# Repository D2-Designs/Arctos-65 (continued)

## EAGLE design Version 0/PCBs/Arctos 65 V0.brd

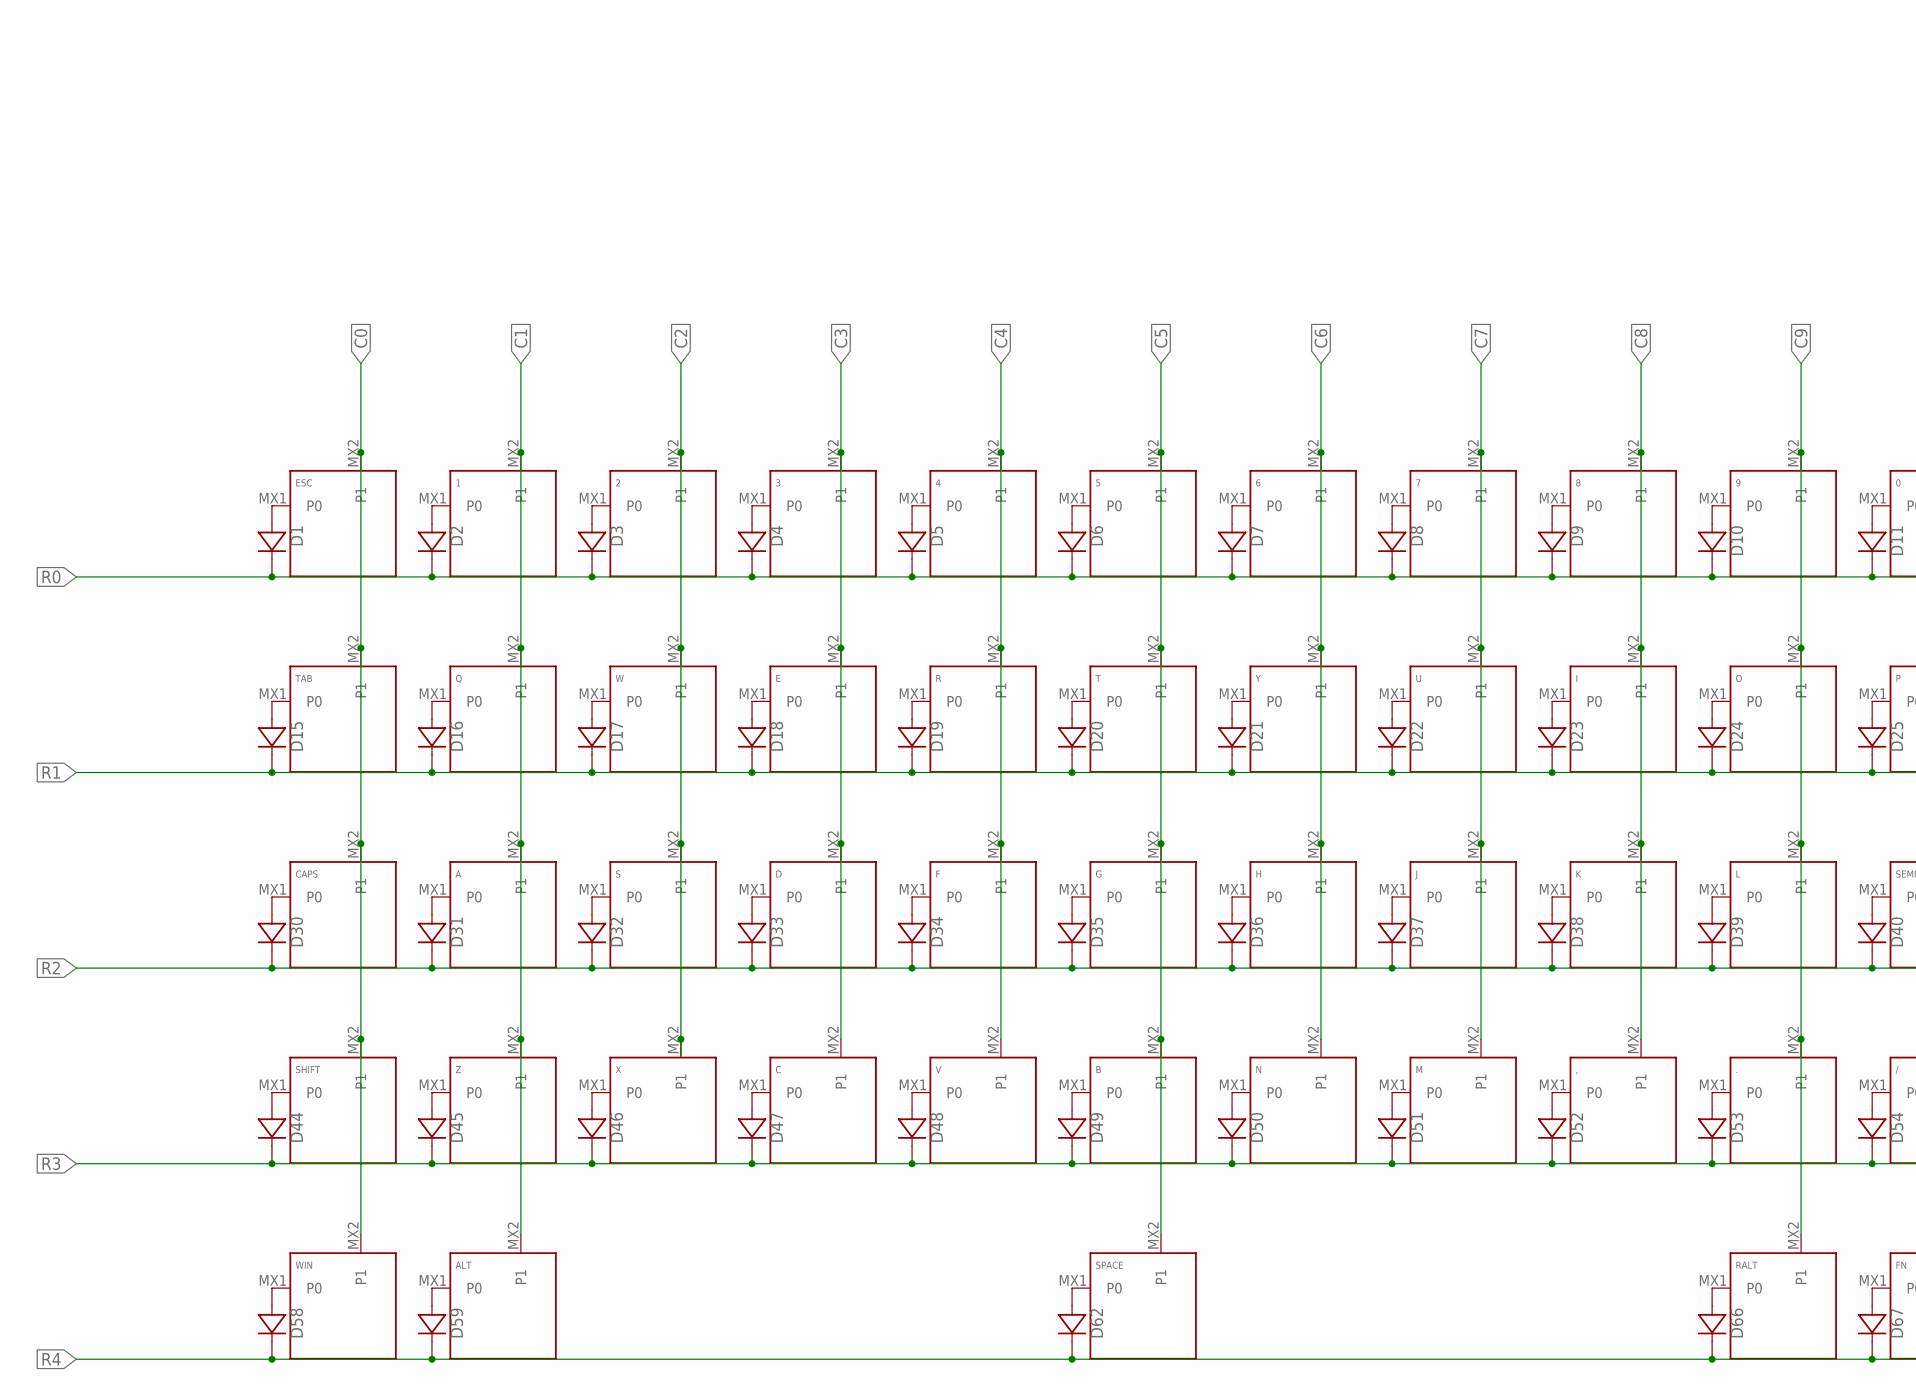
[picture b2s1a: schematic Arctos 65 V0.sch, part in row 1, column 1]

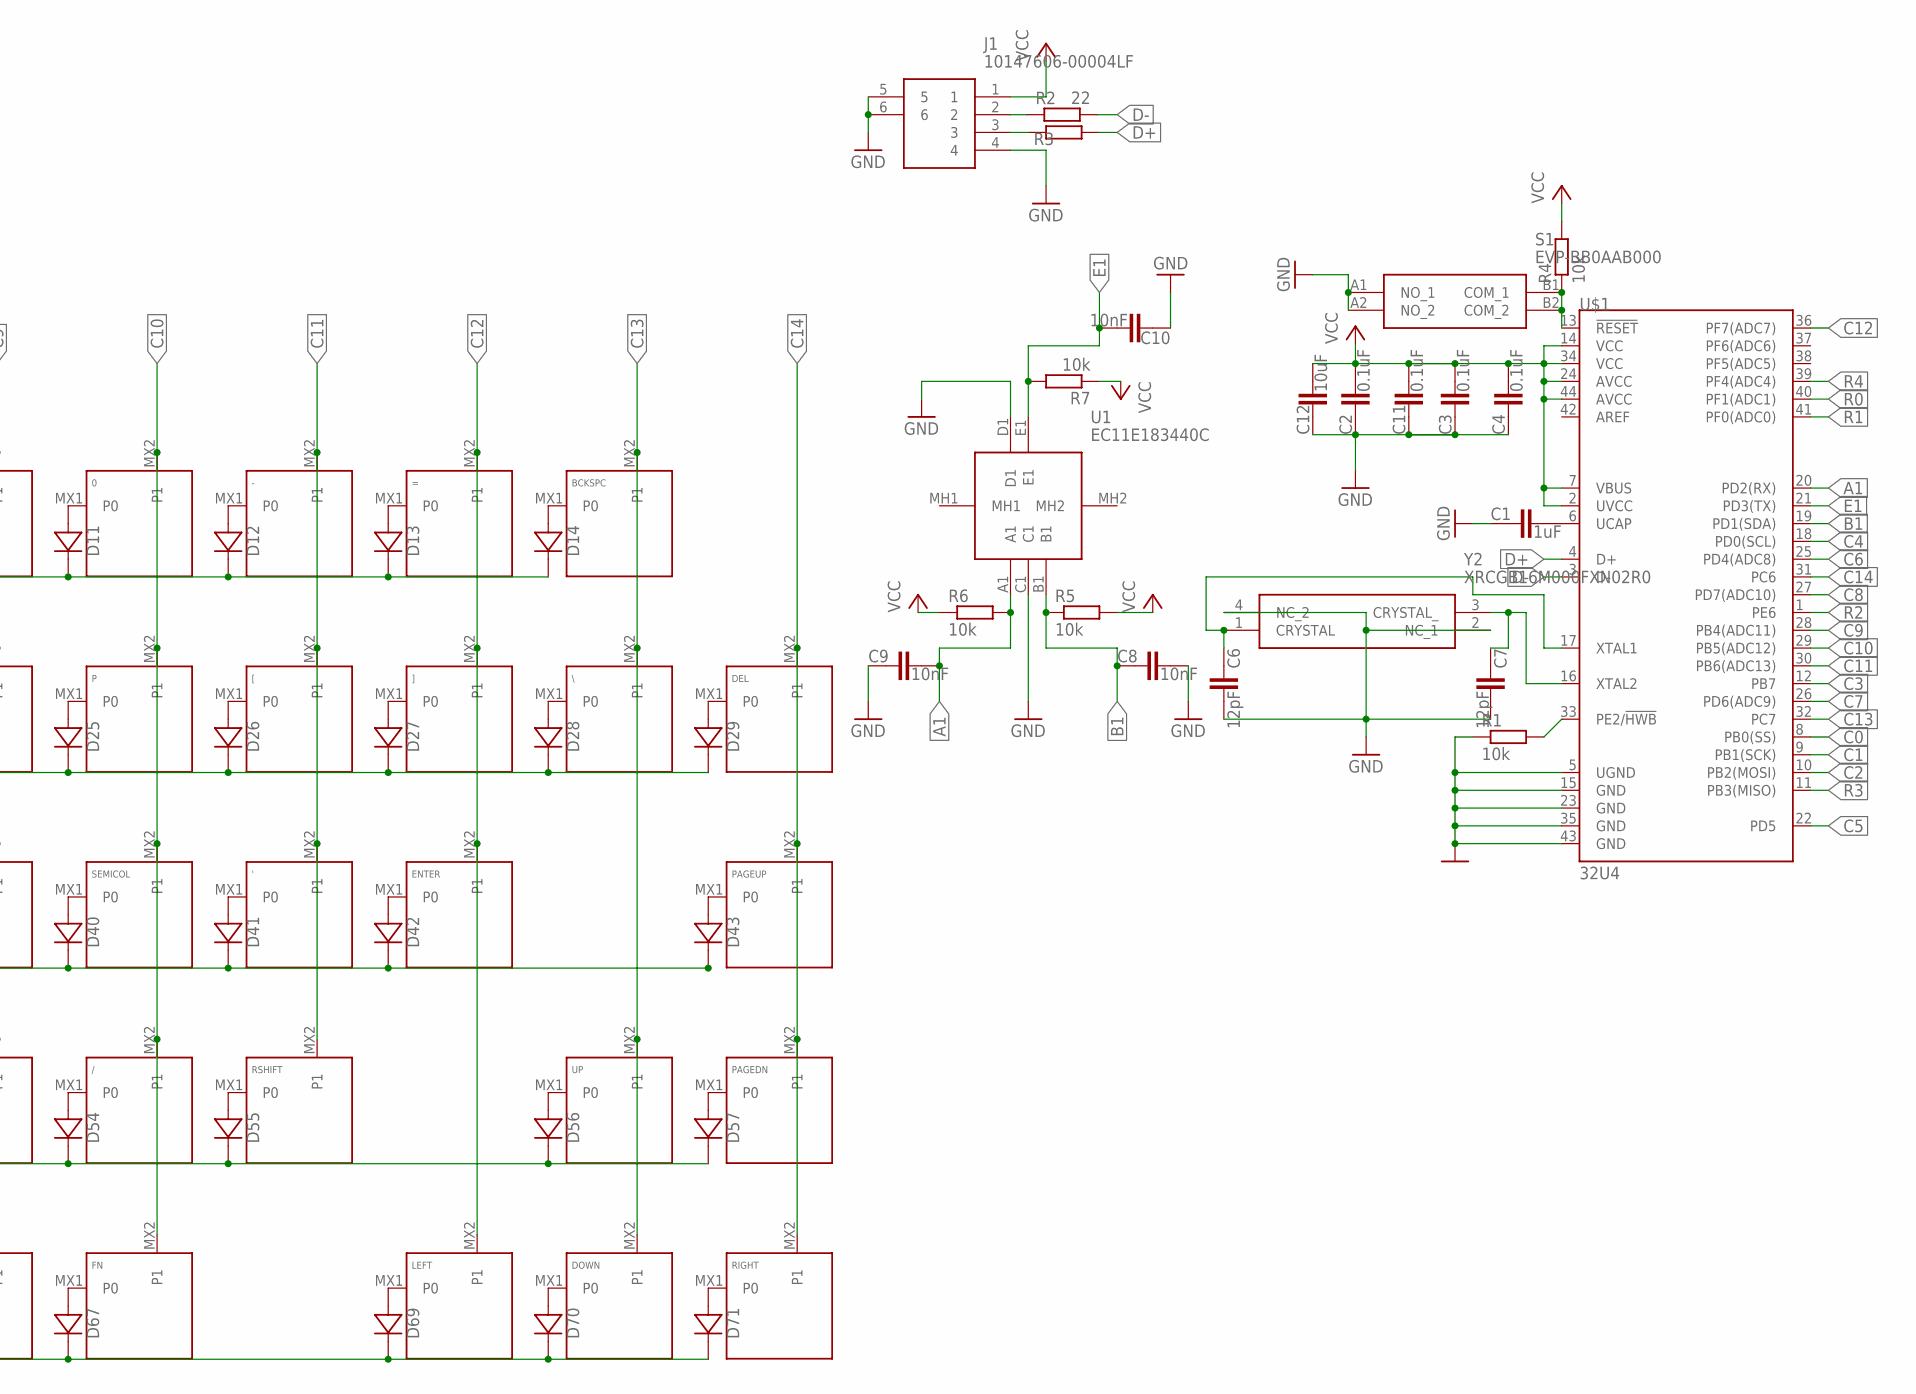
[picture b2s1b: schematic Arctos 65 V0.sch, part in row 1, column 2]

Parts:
0, 1, 2, 3, 4, 5, 6, 7, 8, 9, .: KEYSWITCH-PLAIN-MXHSPCB-1U; MXHSPCB-1U
': KEYSWITCH-PLAIN-MXHSPCB-1U; MXHSPCB-1U
,: KEYSWITCH-PLAIN-MXHSPCB-1U; MXHSPCB-1U
-: KEYSWITCH-PLAIN-MXHSPCB-1U; MXHSPCB-1U
/: KEYSWITCH-PLAIN-MXHSPCB-1U; MXHSPCB-1U
=: KEYSWITCH-PLAIN-MXHSPCB-1U; MXHSPCB-1U
A: KEYSWITCH-PLAIN-MXHSPCB-1U; MXHSPCB-1U
ALT: KEYSWITCH-PLAIN-MXHSPCB-1U; MXHSPCB-1U
B: KEYSWITCH-PLAIN-MXHSPCB-1U; MXHSPCB-1U
BCKSPC: KEYSWITCH-PLAIN-MXHSPCB-2U; MXHSPCB-2U
C: KEYSWITCH-PLAIN-MXHSPCB-1U; MXHSPCB-1U
C1: 1uF; C0603
C2, C3, C4, C11: 0.1uF; C0603
C6, C7: 12pF; C0603
C8, C9, C10: 10nF; C0603
C12: 10uF; C0603
CAPS: KEYSWITCH-PLAIN-MXHSPCB-1U; MXHSPCB-1U
D: KEYSWITCH-PLAIN-MXHSPCB-1U; MXHSPCB-1U
D1, D2, D3, D4, D5, D6, D7, D8, D9, D10, D11, D12, D13, D14, D15, D16, D17, D18, D19, D20, D21, D22, D23, D24, D25, D26, D27, D28, D29, D30, D31, D32, D33, D34, D35, D36, D37, D38, D39, D40, D41, D42, D43, D44, D45, D46, D47, D48, D49, D50, D51, D52, D53, D54, D55, D56, D57, D58, D59, D62, D66, D67, D69, D70, D71: DIODE-SOD-123; SOD-123
DEL: KEYSWITCH-PLAIN-MXHSPCB-1U; MXHSPCB-1U
DOWN: KEYSWITCH-PLAIN-MXHSPCB-1U; MXHSPCB-1U
E: KEYSWITCH-PLAIN-MXHSPCB-1U; MXHSPCB-1U
ENTER: KEYSWITCH-PLAIN-MXHSPCB-2U; MXHSPCB-2U
ESC: KEYSWITCH-PLAIN-MXHSPCB-1U; MXHSPCB-1U
F: KEYSWITCH-PLAIN-MXHSPCB-1U; MXHSPCB-1U
FN: KEYSWITCH-PLAIN-MXHSPCB-1U; MXHSPCB-1U
G: KEYSWITCH-PLAIN-MXHSPCB-1U; MXHSPCB-1U
H: KEYSWITCH-PLAIN-MXHSPCB-1U; MXHSPCB-1U
I: KEYSWITCH-PLAIN-MXHSPCB-1U; MXHSPCB-1U
J: KEYSWITCH-PLAIN-MXHSPCB-1U; MXHSPCB-1U
J1: 10147606-00004LF; 1014760600004LF
K: KEYSWITCH-PLAIN-MXHSPCB-1U; MXHSPCB-1U
L: KEYSWITCH-PLAIN-MXHSPCB-1U; MXHSPCB-1U
LEFT: KEYSWITCH-PLAIN-MXHSPCB-1U; MXHSPCB-1U
M: KEYSWITCH-PLAIN-MXHSPCB-1U; MXHSPCB-1U
N: KEYSWITCH-PLAIN-MXHSPCB-1U; MXHSPCB-1U
O: KEYSWITCH-PLAIN-MXHSPCB-1U; MXHSPCB-1U
P: KEYSWITCH-PLAIN-MXHSPCB-1U; MXHSPCB-1U
PAGEDN: KEYSWITCH-PLAIN-MXHSPCB-1U; MXHSPCB-1U
PAGEUP: KEYSWITCH-PLAIN-MXHSPCB-1U; MXHSPCB-1U
Q: KEYSWITCH-PLAIN-MXHSPCB-1U; MXHSPCB-1U
R: KEYSWITCH-PLAIN-MXHSPCB-1U; MXHSPCB-1U
R1, R4, R5, R6, R7: 10k; R0603
R2, R3: 22; R0603
RALT: KEYSWITCH-PLAIN-MXHSPCB-1U; MXHSPCB-1U
RIGHT: KEYSWITCH-PLAIN-MXHSPCB-1U; MXHSPCB-1U
RSHIFT: KEYSWITCH-PLAIN-MXHSPCB-1U; MXHSPCB-1U
S: KEYSWITCH-PLAIN-MXHSPCB-1U; MXHSPCB-1U
S1: EVP-BB0AAB000; EVPBB0AAB000
SEMICOL: KEYSWITCH-PLAIN-MXHSPCB-1U; MXHSPCB-1U
SHIFT: KEYSWITCH-PLAIN-MXHSPCB-2U; MXHSPCB-2U
SPACE: KEYSWITCH-PLAIN-MXHSPCB-7U-FLIPPED; MXHSPCB-7U-FLIPPED
T: KEYSWITCH-PLAIN-MXHSPCB-1U; MXHSPCB-1U
TAB: KEYSWITCH-PLAIN-MXHSPCB-1U; MXHSPCB-1U
U: KEYSWITCH-PLAIN-MXHSPCB-1U; MXHSPCB-1U
U1: EC11E183440C
U$1: 32U4; TQFP44
UP: KEYSWITCH-PLAIN-MXHSPCB-1U; MXHSPCB-1U
V: KEYSWITCH-PLAIN-MXHSPCB-1U; MXHSPCB-1U
W: KEYSWITCH-PLAIN-MXHSPCB-1U; MXHSPCB-1U
WIN: KEYSWITCH-PLAIN-MXHSPCB-1U; MXHSPCB-1U
X: KEYSWITCH-PLAIN-MXHSPCB-1U; MXHSPCB-1U
Y: KEYSWITCH-PLAIN-MXHSPCB-1U; MXHSPCB-1U
Y2: XRCGB16M000FXN02R0
Z: KEYSWITCH-PLAIN-MXHSPCB-1U; MXHSPCB-1U
[: KEYSWITCH-PLAIN-MXHSPCB-1U; MXHSPCB-1U
\: KEYSWITCH-PLAIN-MXHSPCB-1U; MXHSPCB-1U
]: KEYSWITCH-PLAIN-MXHSPCB-1U; MXHSPCB-1U

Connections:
A1: C9.2, R6.2, U1.A1, U$1.20 (PD2(RX))
B1: C8.1, R5.1, U1.B1, U$1.19 (PD1(SDA))
C0: CAPS.MX2 (P1), ESC.MX2 (P1), SHIFT.MX2 (P1), TAB.MX2 (P1), U$1.8 (PB0(SS)), WIN.MX2 (P1)
C1: 1.MX2 (P1), A.MX2 (P1), ALT.MX2 (P1), Q.MX2 (P1), U$1.9 (PB1(SCK)), Z.MX2 (P1)
C2: 2.MX2 (P1), S.MX2 (P1), U$1.10 (PB2(MOSI)), W.MX2 (P1), X.MX2 (P1)
C3: 3.MX2 (P1), C.MX2 (P1), D.MX2 (P1), E.MX2 (P1), U$1.12 (PB7)
C4: 4.MX2 (P1), F.MX2 (P1), R.MX2 (P1), U$1.18 (PD0(SCL)), V.MX2 (P1)
C5: 5.MX2 (P1), B.MX2 (P1), G.MX2 (P1), SPACE.MX2 (P1), T.MX2 (P1), U$1.22 (PD5)
C6: 6.MX2 (P1), H.MX2 (P1), N.MX2 (P1), U$1.25 (PD4(ADC8)), Y.MX2 (P1)
C7: 7.MX2 (P1), J.MX2 (P1), M.MX2 (P1), U.MX2 (P1), U$1.26 (PD6(ADC9))
C8: 8.MX2 (P1), ,.MX2 (P1), I.MX2 (P1), K.MX2 (P1), U$1.27 (PD7(ADC10))
C9: 9.MX2 (P1), ..MX2 (P1), L.MX2 (P1), O.MX2 (P1), RALT.MX2 (P1), U$1.28 (PB4(ADC11))
C10: 0.MX2 (P1), /.MX2 (P1), FN.MX2 (P1), P.MX2 (P1), SEMICOL.MX2 (P1), U$1.29 (PB5(ADC12))
C11: '.MX2 (P1), -.MX2 (P1), RSHIFT.MX2 (P1), U$1.30 (PB6(ADC13)), [.MX2 (P1)
C12: =.MX2 (P1), ENTER.MX2 (P1), LEFT.MX2 (P1), U$1.36 (PF7(ADC7)), ].MX2 (P1)
C13: BCKSPC.MX2 (P1), DOWN.MX2 (P1), U$1.32 (PC7), UP.MX2 (P1), \.MX2 (P1)
C14: DEL.MX2 (P1), PAGEDN.MX2 (P1), PAGEUP.MX2 (P1), RIGHT.MX2 (P1), U$1.31 (PC6)
D+: R3.2, U$1.4 (D+)
D-: R2.2, U$1.3 (D-)
E1: C10.2, R7.2, U1.E1, U$1.21 (PD3(TX))
GND: C1.1, C2.1, C3.1, C4.1, C6.2, C7.2, C8.2, C9.1, C10.1, C11.1, C12.1, J1.4, J1.5, J1.6, R1.1, S1.A1 (NO_1), S1.A2 (NO_2), U1.C1, U1.D1, U$1.5 (UGND), U$1.15 (GND), U$1.23 (GND), U$1.35 (GND), U$1.43 (GND), Y2.2 (NC_1), Y2.4 (NC_2)
unnamed: 4.MX1 (P0), D5.A
unnamed: 5.MX1 (P0), D6.A
unnamed: 6.MX1 (P0), D7.A
unnamed: 7.MX1 (P0), D8.A
unnamed: 8.MX1 (P0), D9.A
unnamed: 9.MX1 (P0), D10.A
unnamed: 0.MX1 (P0), D11.A
unnamed: -.MX1 (P0), D12.A
unnamed: =.MX1 (P0), D13.A
unnamed: BCKSPC.MX1 (P0), D14.A
unnamed: D15.A, TAB.MX1 (P0)
unnamed: D16.A, Q.MX1 (P0)
unnamed: D17.A, W.MX1 (P0)
unnamed: D18.A, E.MX1 (P0)
unnamed: D19.A, R.MX1 (P0)
unnamed: D20.A, T.MX1 (P0)
unnamed: D21.A, Y.MX1 (P0)
unnamed: D22.A, U.MX1 (P0)
unnamed: D23.A, I.MX1 (P0)
unnamed: D24.A, O.MX1 (P0)
unnamed: D25.A, P.MX1 (P0)
unnamed: D26.A, [.MX1 (P0)
unnamed: D27.A, ].MX1 (P0)
unnamed: D28.A, \.MX1 (P0)
unnamed: D29.A, DEL.MX1 (P0)
unnamed: CAPS.MX1 (P0), D30.A
unnamed: A.MX1 (P0), D31.A
unnamed: D32.A, S.MX1 (P0)
unnamed: D.MX1 (P0), D33.A
unnamed: D34.A, F.MX1 (P0)
unnamed: D35.A, G.MX1 (P0)
unnamed: D36.A, H.MX1 (P0)
unnamed: D37.A, J.MX1 (P0)
unnamed: D38.A, K.MX1 (P0)
unnamed: D39.A, L.MX1 (P0)
unnamed: D40.A, SEMICOL.MX1 (P0)
unnamed: '.MX1 (P0), D41.A
unnamed: D42.A, ENTER.MX1 (P0)
unnamed: D43.A, PAGEUP.MX1 (P0)
unnamed: D45.A, Z.MX1 (P0)
unnamed: D46.A, X.MX1 (P0)
unnamed: C.MX1 (P0), D47.A
unnamed: D48.A, V.MX1 (P0)
unnamed: D1.A, ESC.MX1 (P0)
unnamed: B.MX1 (P0), D49.A
unnamed: D50.A, N.MX1 (P0)
unnamed: 1.MX1 (P0), D2.A
unnamed: D51.A, M.MX1 (P0)
unnamed: ,.MX1 (P0), D52.A
unnamed: ..MX1 (P0), D53.A
unnamed: /.MX1 (P0), D54.A
unnamed: D55.A, RSHIFT.MX1 (P0)
unnamed: 2.MX1 (P0), D3.A
unnamed: 3.MX1 (P0), D4.A
unnamed: D56.A, UP.MX1 (P0)
unnamed: D44.A, SHIFT.MX1 (P0)
unnamed: D57.A, PAGEDN.MX1 (P0)
unnamed: D58.A, WIN.MX1 (P0)
unnamed: ALT.MX1 (P0), D59.A
unnamed: D66.A, RALT.MX1 (P0)
unnamed: D67.A, FN.MX1 (P0)
unnamed: D69.A, LEFT.MX1 (P0)
unnamed: D70.A, DOWN.MX1 (P0)
unnamed: D71.A, RIGHT.MX1 (P0)
unnamed: D62.A, SPACE.MX1 (P0)
unnamed: R4.1, S1.B1 (COM_1), S1.B2 (COM_2), U$1.13 (!RESET)
unnamed: R1.2, U$1.33 (PE2/!HWB)
unnamed: J1.2, R2.1
unnamed: J1.3, R3.1
unnamed: C1.2, U$1.6 (UCAP)
unnamed: C6.1, U$1.17 (XTAL1), Y2.1 (CRYSTAL)
unnamed: C7.1, U$1.16 (XTAL2), Y2.3 (CRYSTAL_)
R0: D1.C, D2.C, D3.C, D4.C, D5.C, D6.C, D7.C, D8.C, D9.C, D10.C, D11.C, D12.C, D13.C, D14.C, U$1.40 (PF1(ADC1))
R1: D15.C, D16.C, D17.C, D18.C, D19.C, D20.C, D21.C, D22.C, D23.C, D24.C, D25.C, D26.C, D27.C, D28.C, D29.C, U$1.41 (PF0(ADC0))
R2: D30.C, D31.C, D32.C, D33.C, D34.C, D35.C, D36.C, D37.C, D38.C, D39.C, D40.C, D41.C, D42.C, D43.C, U$1.1 (PE6)
R3: D44.C, D45.C, D46.C, D47.C, D48.C, D49.C, D50.C, D51.C, D52.C, D53.C, D54.C, D55.C, D56.C, D57.C, U$1.11 (PB3(MISO))
R4: D58.C, D59.C, D62.C, D66.C, D67.C, D69.C, D70.C, D71.C, U$1.39 (PF4(ADC4))
VCC: C2.2, C3.2, C4.2, C11.2, C12.2, J1.1, R4.2, R5.2, R6.1, R7.1, U$1.2 (UVCC), U$1.7 (VBUS), U$1.14 (VCC), U$1.24 (AVCC), U$1.34 (VCC), U$1.44 (AVCC)

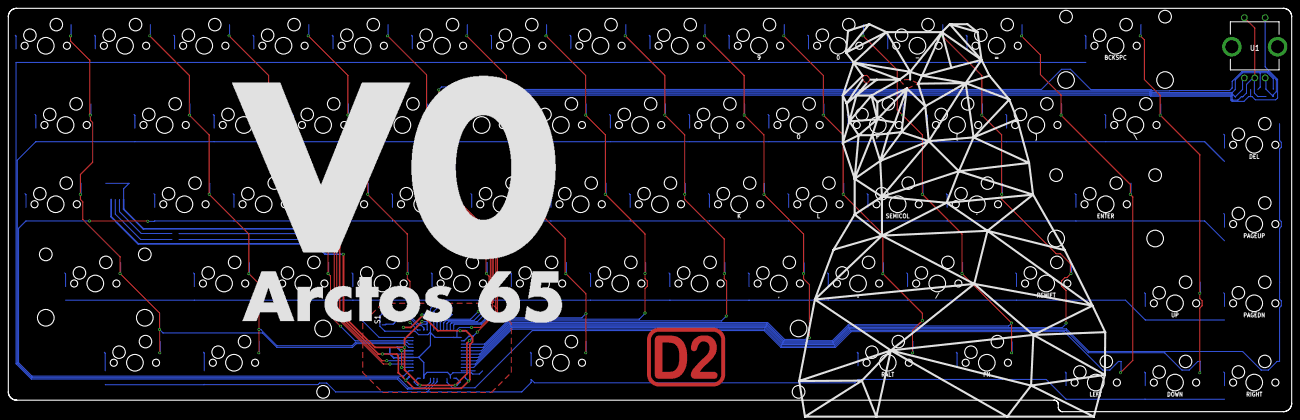
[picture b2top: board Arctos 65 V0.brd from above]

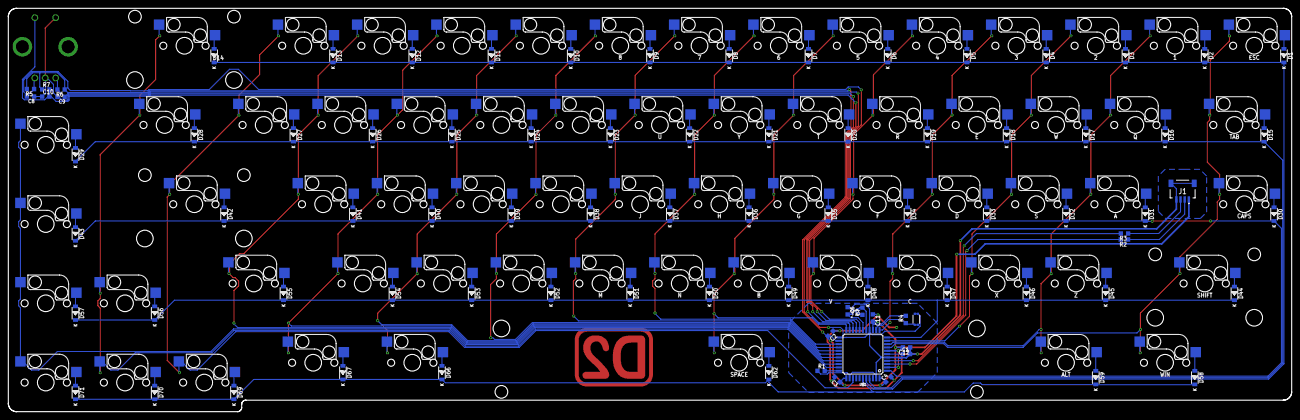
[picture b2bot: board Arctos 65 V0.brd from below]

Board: 2 copper layers, 308.5 x 97.0 mm, 153 parts (152 on the bottom side), 99 nets.

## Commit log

2020-11-16 Create Issues
2020-11-16 Create Case Issues
2020-11-16 Organization
2020-11-16 Update Case Issues
2020-11-16 Update Issues
2020-11-16 Added Eagle Files and Plate DXF
2020-12-02 Version 1 Update
    Version 1 PCB and Gerbers Uploaded
